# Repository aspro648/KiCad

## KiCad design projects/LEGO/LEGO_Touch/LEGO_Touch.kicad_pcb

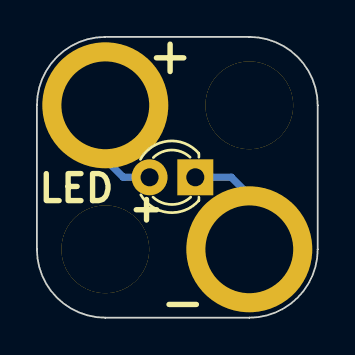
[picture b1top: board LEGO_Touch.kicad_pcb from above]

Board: 2 copper layers, 15.6 x 15.6 mm, 5 parts (0 on the bottom side), 2 nets.

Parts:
D1: LED; LED-3MM
P1, P2, P3, P4: Pad; Lego_Pad

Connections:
unnamed: D1.1, P4.1
unnamed: D1.2, P1.1

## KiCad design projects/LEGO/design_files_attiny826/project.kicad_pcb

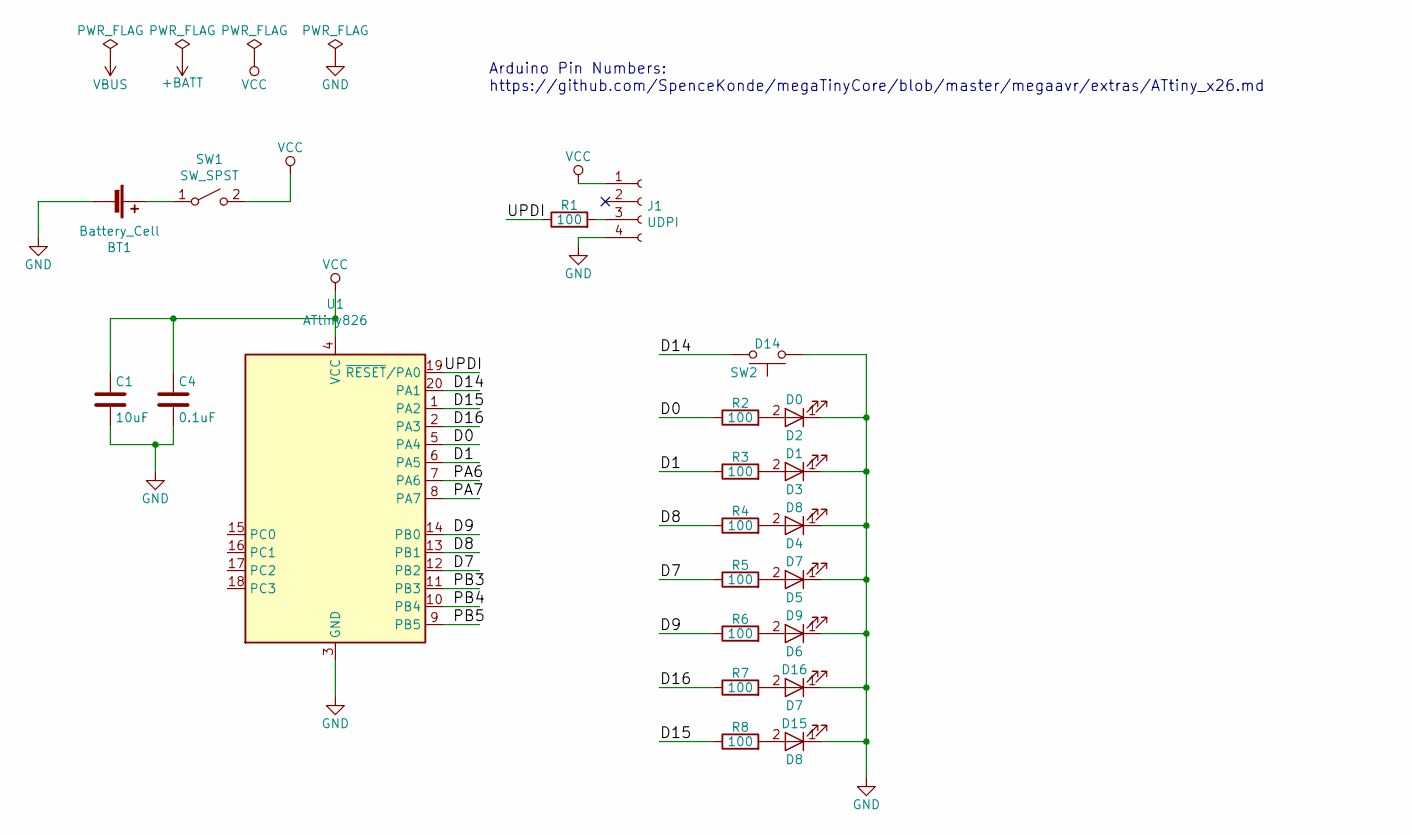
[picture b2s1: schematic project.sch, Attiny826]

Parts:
BT1: Battery_Cell; BatteryHolder_Keystone_3034_1x20mm
C1: 10uF; C_0805
C4: 0.1uF; C_0603
D2: D0; LED_1206_3216Metric
D3: D1; LED_1206_3216Metric
D4: D8; LED_1206_3216Metric
D5: D7; LED_1206_3216Metric
D6: D9; LED_1206_3216Metric
D7: D16; LED_1206_3216Metric
D8: D15; LED_1206_3216Metric
J1: UDPI; UDPI_header
R1, R2, R3, R4, R5, R6, R7, R8: 100; R_0603
SW1: SW_SPST; SPST_SMD
SW2: D14; EVQ-P7A
U1: ATtiny826; VQFN-20-1EP_3x3mm_P0.4mm_EP1.7x1.7mm

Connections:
/D0: R2.1, U1.5 (PA4)
/D1: R3.1, U1.6 (PA5)
/D7: R5.1, U1.12 (PB2)
/D8: R4.1, U1.13 (PB1)
/D9: R6.1, U1.14 (PB0)
/D14: SW2.2, U1.20 (PA1)
/D15: R8.1, U1.1 (PA2)
/D16: R7.1, U1.2 (PA3)
/PA6: U1.7 (PA6)
/PA7: U1.8 (PA7)
/PB3: U1.11 (PB3)
/PB4: U1.10 (PB4)
/PB5: U1.9 (PB5)
/UPDI: R1.1, U1.19 (~RESET~/PA0)
GND: BT1.2 (-), C1.2, C4.2, D2.1 (K), D3.1 (K), D4.1 (K), D5.1 (K), D6.1 (K), D7.1 (K), D8.1 (K), J1.4, SW2.1, U1.3 (GND), U1.21 (GND)
unnamed: BT1.1 (+), SW1.1 (A)
unnamed: D2.2 (A), R2.2
unnamed: D3.2 (A), R3.2
unnamed: D4.2 (A), R4.2
unnamed: D5.2 (A), R5.2
unnamed: D6.2 (A), R6.2
unnamed: D7.2 (A), R7.2
unnamed: D8.2 (A), R8.2
unnamed: J1.3, R1.2
VCC: C1.1, C4.1, J1.1, SW1.2 (B), U1.4 (VCC)

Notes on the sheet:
Arduino Pin Numbers: https://github.com/SpenceKonde/megaTinyCore/blob/master/megaavr/extras/ATtiny_x26.md

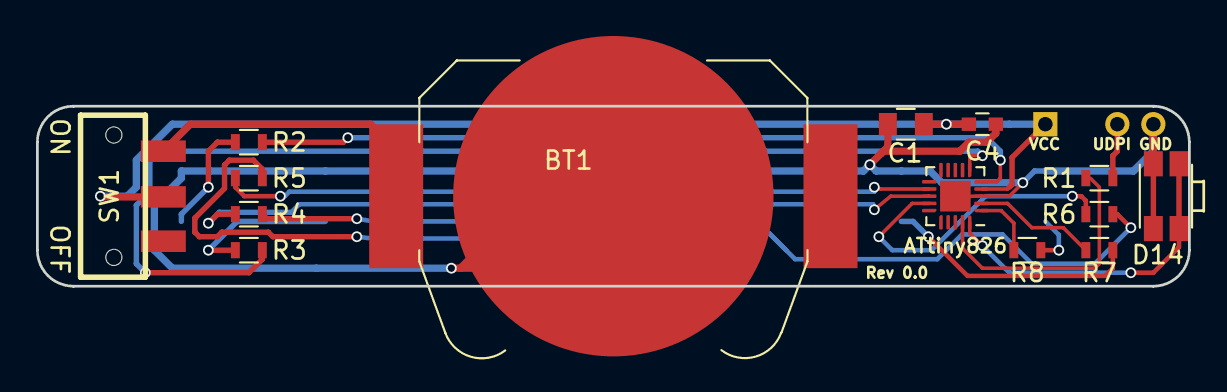
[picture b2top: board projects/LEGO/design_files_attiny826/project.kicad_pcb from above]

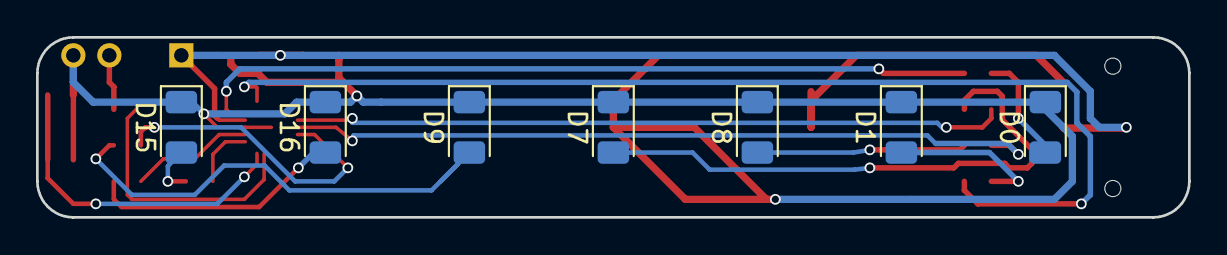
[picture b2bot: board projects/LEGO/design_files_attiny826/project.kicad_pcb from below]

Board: 2 copper layers, 64.0 x 10.0 mm, 22 parts (7 on the bottom side), 20 nets.

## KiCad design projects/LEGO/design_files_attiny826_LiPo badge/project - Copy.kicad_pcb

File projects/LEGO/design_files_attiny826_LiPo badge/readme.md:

Attiny826 Name Tag

Bill Of Materials
----------------

- 1 ea., Perfect Purple PCB from OSH Park from [design_files/project.kicad_pcb](project.kicad_pcb) file.
- 1 ea., Attiny826 IC MCU 8BIT 8KB FLASH 20VQFN, https://www.digikey.com/short/b9cq02np
- 3 ea., CAP CER 10uF 50V 0805,
- 1 ea., CAP CER 0.1uF 0605
- 1 ea., 3.7V LiPo (VERIFY CONNECTOR AND POLARITY).
- 1 ea., CONN RCPT MICRO USB R/A SMD, Molex 1050170001, https://www.digikey.com/short/jb2205
- 1 ea., PTC RESET FUSE 15V 100MA 0805, Bel Fuse 0ZCK0010FF2G, https://www.digikey.com/short/v24142q9
- 1 ea., JST SH CONN HEADER SMD R/A 2POS 1MM, SM02B-SRSS-TB(LF)(SN), https://www.digikey.com/short/z4vw0z
- 1 ea., CONN HOUSING SH 2POS 1MM WHITE, SHR-02V-S-B, https://www.digikey.com/short/0b2m0rpt
- 12 ea., RES SMD 100 OHM 5% 1/8W 0402,
- 2 ea., RES SMD 1K OHM, 0603
- 2 ea., RES SMD 10K OHM, 0603
- 1 ea., SMD SPST switch, C&K JS102011SCQN, https://www.digikey.com/short/5m7mwm1b

- LEDs: 
    - 3 ea., LED RED DIFFUSED 0603 SMD (CHG)
	- 1 ea., LED GREEN DIFFUSE 0603 SMD (DONE)
    - 12 ea., LED WHITE? SMD 0402, https://www.digikey.com/short/d4vn9ddn
	- 1 ea., NeoPixel Nano 2020, https://www.adafruit.com/product/4684 or https://www.digikey.com/short/480tzjf0

Revisions
----------------
- Revision 0.0

License
----------------
[Attribution-ShareAlike 3.0 United States (CC BY-SA 3.0 US)](https://creativecommons.org/licenses/by-sa/3.0/us/)

You are free to:

- Share — copy and redistribute the material in any medium or format
- Adapt — remix, transform, and build upon the material

Under the following terms:

- Attribution — You must give appropriate credit, provide a link to the license, and indicate if changes were made. You may do so in any reasonable manner, but not in any way that suggests the licensor endorses you or your use.
- ShareAlike — If you remix, transform, or build upon the material, you must distribute your contributions under the same license as the original.

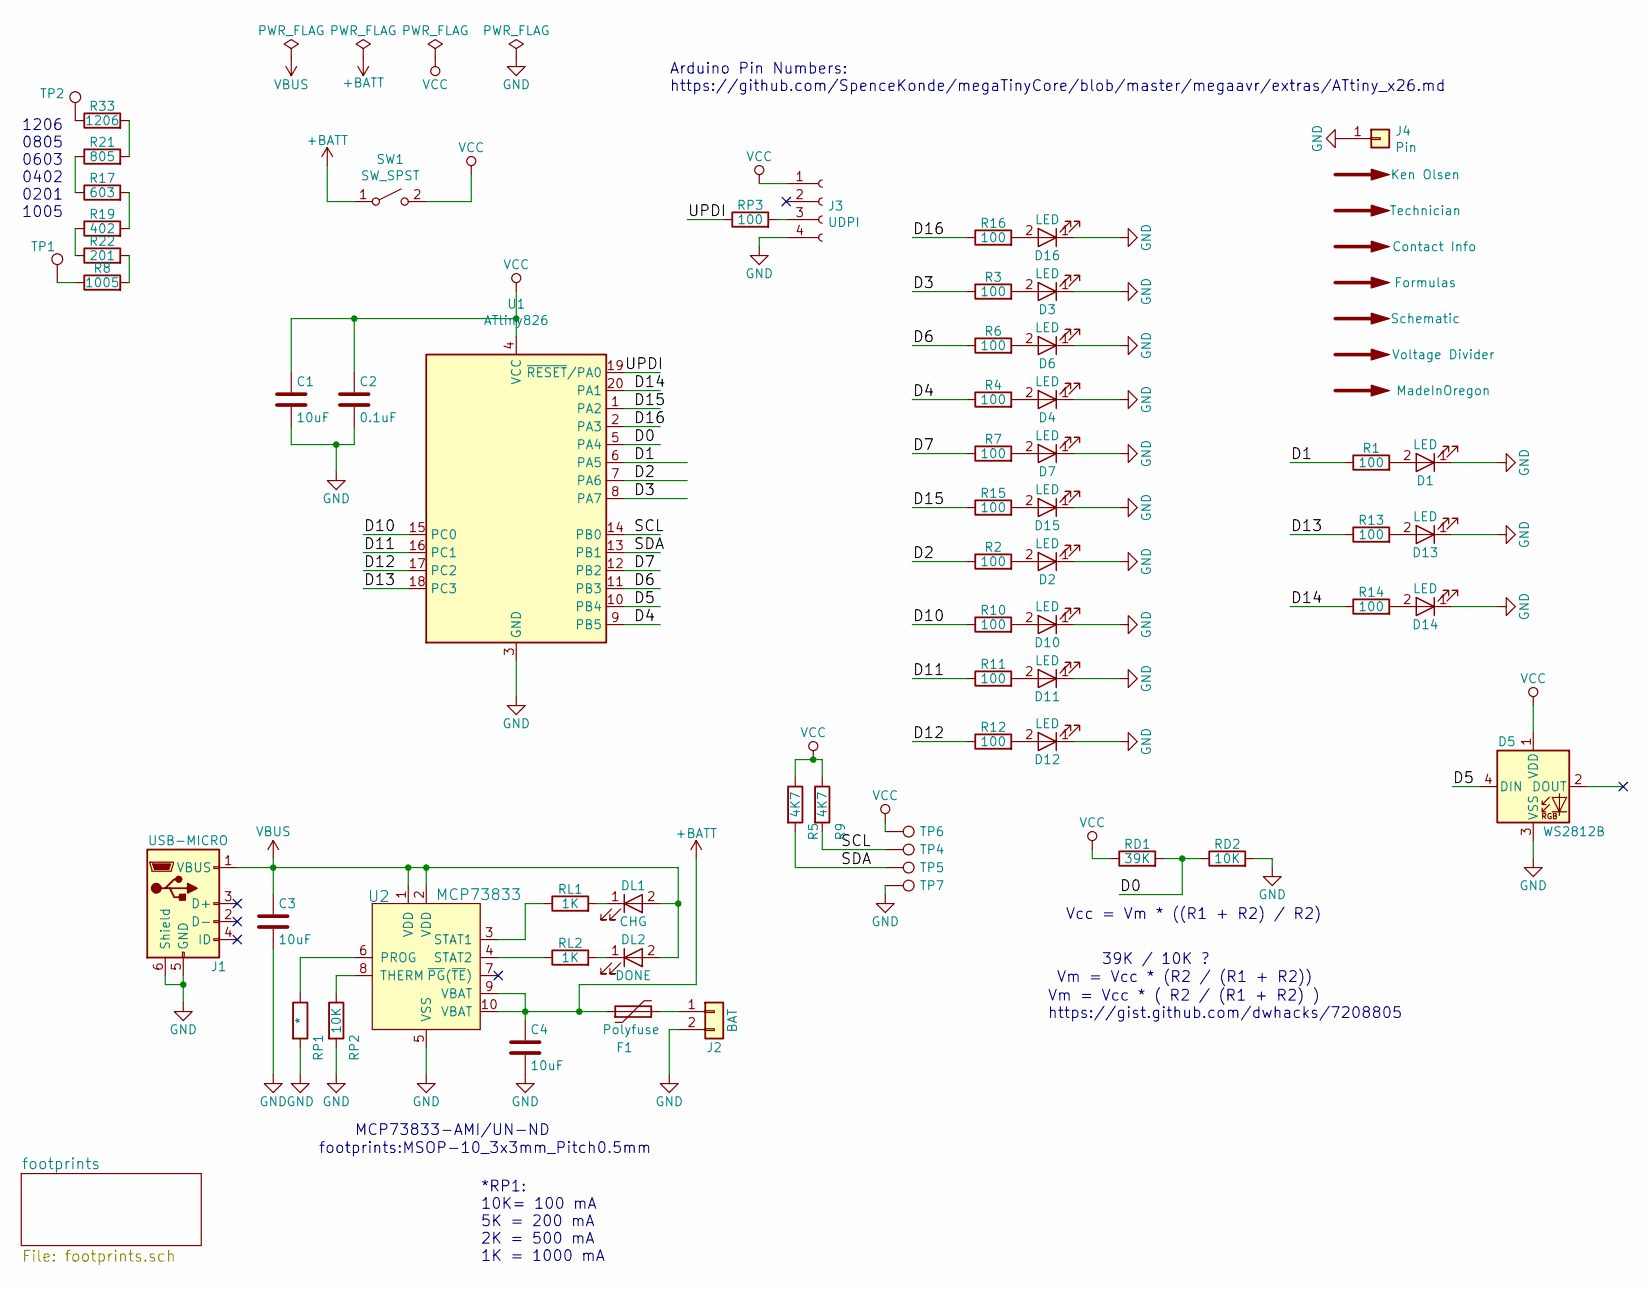
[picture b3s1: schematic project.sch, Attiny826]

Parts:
C1, C3, C4: 10uF; C_0805
C2: 0.1uF; C_0603
D1, D2, D3, D4, D6, D7, D10, D11, D12, D13, D14, D15, D16: LED; LED_0402_1005Metric
D5: WS2812B; WS2812B-2020
DL1: CHG; LED_0603
DL2: DONE; LED_0603
F1: Polyfuse; Fuse_0805_2012Metric
J1: USB-MICRO; USB_Micro-B_Molex-105017-0001
J2: BAT; JST_SH_SM02B-SRSS-TB_02x1.00mm_Angled
J3: UDPI; UDPI_header
J4: Pin; Pin_holder_SMD
R1, R2, R3, R4, R6, R7, R10, R11, R12, R13, R14, R15, R16: 100; R_0402_1005Metric
R5, R9: 4K7; R_0603
R8: 1005; R_01005_0402Metric
R17: 603; R_0603_1608Metric
R19: 402; R_0402
R21: 805; R_0805_2012Metric
R22: 201; R_0201_0603Metric
R33: 1206; R_1206_3216Metric
RD1: 39K; R_0402_1005Metric
RD2: 10K; R_0402_1005Metric
RL1, RL2: 1K; R_0603
RP1: *; R_0603
RP2: 10K; R_0603
RP3: 100; R_0402_1005Metric
SW1: SW_SPST; SPST_SMD
SYM1: Ken Olsen; KenOlsen
SYM2: Technician; ElectronicTechnician
SYM3: Contact Info; contact
SYM4: Formulas; PieChart
SYM5: Schematic; schematic
SYM6: Voltage Divider; schematic2
SYM7: MadeInOregon; MadeInOregonRev25
TP1, TP2: TestPoint; TestPoint_Pad_D1.0mm
TP4: SCL; TestPoint_Pad_D1.0mm
TP5: SDA; TestPoint_Pad_D1.0mm
TP6: VCC; TestPoint_Pad_D1.0mm
TP7: GND; TestPoint_Pad_D1.0mm
U1: ATtiny826; VQFN-20-1EP_3x3mm_P0.4mm_EP1.7x1.7mm
U2: MCP73833; MSOP-10_3x3mm_Pitch0.5mm

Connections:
+BATT: C4.1, F1.1, SW1.1 (A), U2.9 (VBAT), U2.10 (VBAT)
/D0: RD1.2, RD2.1, U1.5 (PA4)
/D1: R1.1, U1.6 (PA5)
/D2: R2.1, U1.7 (PA6)
/D3: R3.1, U1.8 (PA7)
/D4: R4.1, U1.9 (PB5)
/D5: D5.4 (DIN), U1.10 (PB4)
/D6: R6.1, U1.11 (PB3)
/D7: R7.1, U1.12 (PB2)
/D10: R10.1, U1.15 (PC0)
/D11: R11.1, U1.16 (PC1)
/D12: R12.1, U1.17 (PC2)
/D13: R13.1, U1.18 (PC3)
/D14: R14.1, U1.20 (PA1)
/D15: R15.1, U1.1 (PA2)
/D16: R16.1, U1.2 (PA3)
/SCL: R9.2, TP4.1, U1.14 (PB0)
/SDA: R5.2, TP5.1, U1.13 (PB1)
/UPDI: RP3.1, U1.19 (~RESET~/PA0)
GND: C1.2, C2.2, C3.2, C4.2, D1.1 (K), D2.1 (K), D3.1 (K), D4.1 (K), D5.3 (VSS), D6.1 (K), D7.1 (K), D10.1 (K), D11.1 (K), D12.1 (K), D13.1 (K), D14.1 (K), D15.1 (K), D16.1 (K), J1.5 (GND), J1.6 (Shield), J2.2, J3.4, J4.1, RD2.2, RP1.2, RP2.2, TP7.1, U1.3 (GND), U1.21 (GND), U2.5 (VSS)
unnamed: D1.2 (A), R1.2
unnamed: D2.2 (A), R2.2
unnamed: D3.2 (A), R3.2
unnamed: D4.2 (A), R4.2
unnamed: D6.2 (A), R6.2
unnamed: D7.2 (A), R7.2
unnamed: D10.2 (A), R10.2
unnamed: D11.2 (A), R11.2
unnamed: D12.2 (A), R12.2
unnamed: D13.2 (A), R13.2
unnamed: D14.2 (A), R14.2
unnamed: D15.2 (A), R15.2
unnamed: D16.2 (A), R16.2
unnamed: DL1.1 (K), RL1.2
unnamed: DL2.1 (K), RL2.2
unnamed: F1.2, J2.1
unnamed: J3.3, RP3.2
unnamed: R8.1, TP1.1
unnamed: R17.1, R21.1
unnamed: R17.2, R19.2
unnamed: R19.1, R22.1
unnamed: R21.2, R33.2
unnamed: R8.2, R22.2
unnamed: R33.1, TP2.1
unnamed: RL1.1, U2.3 (STAT1)
unnamed: RL2.1, U2.4 (STAT2)
unnamed: RP1.1, U2.6 (PROG)
unnamed: RP2.1, U2.8 (THERM)
VBUS: C3.1, DL1.2 (A), DL2.2 (A), J1.1 (VBUS), U2.1 (VDD), U2.2 (VDD)
VCC: C1.1, C2.1, D5.1 (VDD), J3.1, R5.1, R9.1, RD1.1, SW1.2 (B), TP6.1, U1.4 (VCC)

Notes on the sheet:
Arduino Pin Numbers: https://github.com/SpenceKonde/megaTinyCore/blob/master/megaavr/extras/ATtiny_x26.md
*RP1: 10K= 100 mA 5K = 200 mA 2K = 500 mA 1K = 1000 mA
footprints:MSOP-10_3x3mm_Pitch0.5mm
MCP73833-AMI/UN-ND
39K / 10K ?
Vm = Vcc * ( R2 / (R1 + R2) ) https://gist.github.com/dwhacks/7208805
1206 0805 0603 0402 0201 1005
Vm = Vcc * (R2 / (R1 + R2))
Vcc = Vm * ((R1 + R2) / R2)

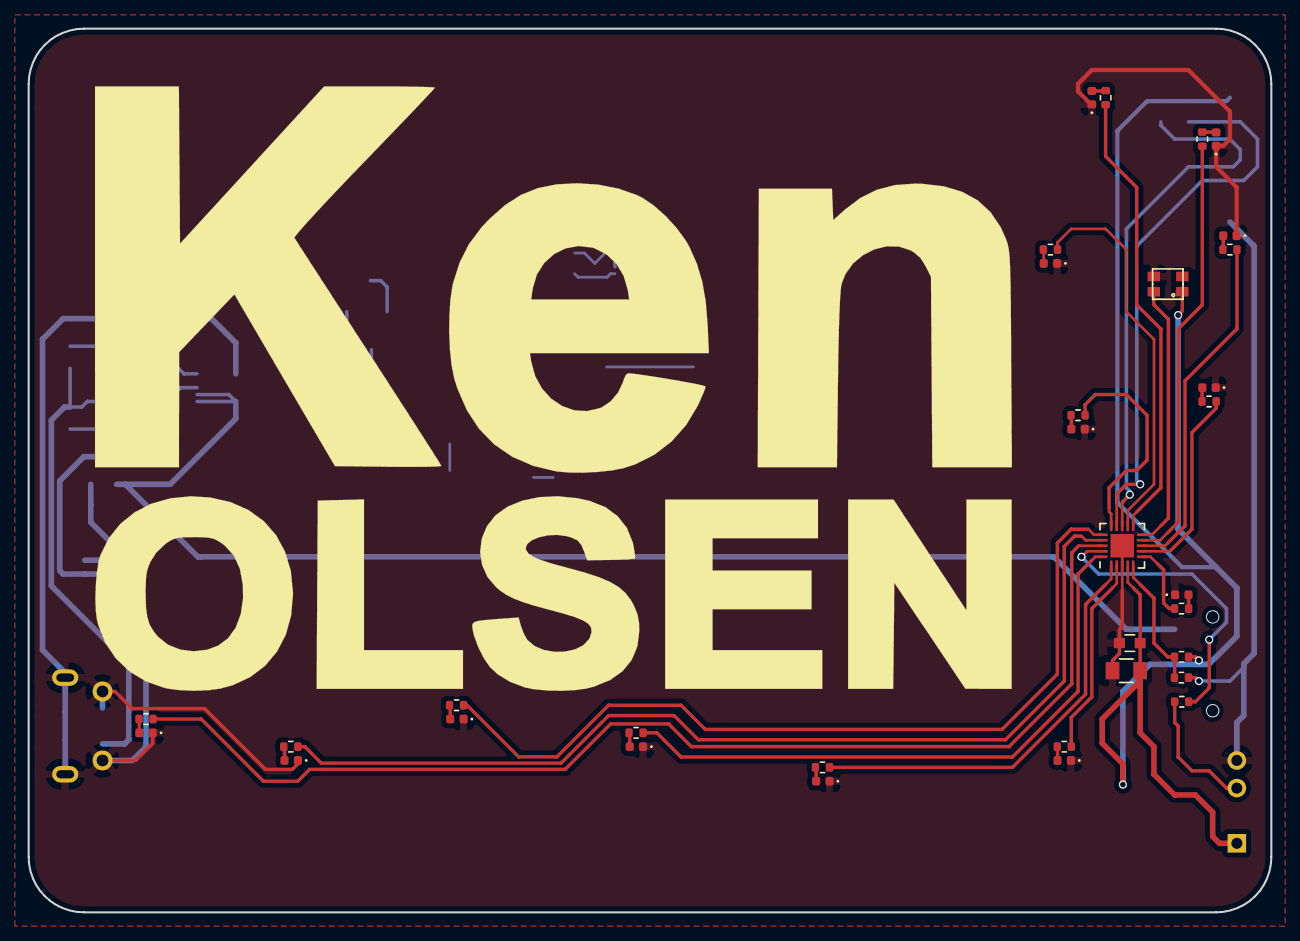
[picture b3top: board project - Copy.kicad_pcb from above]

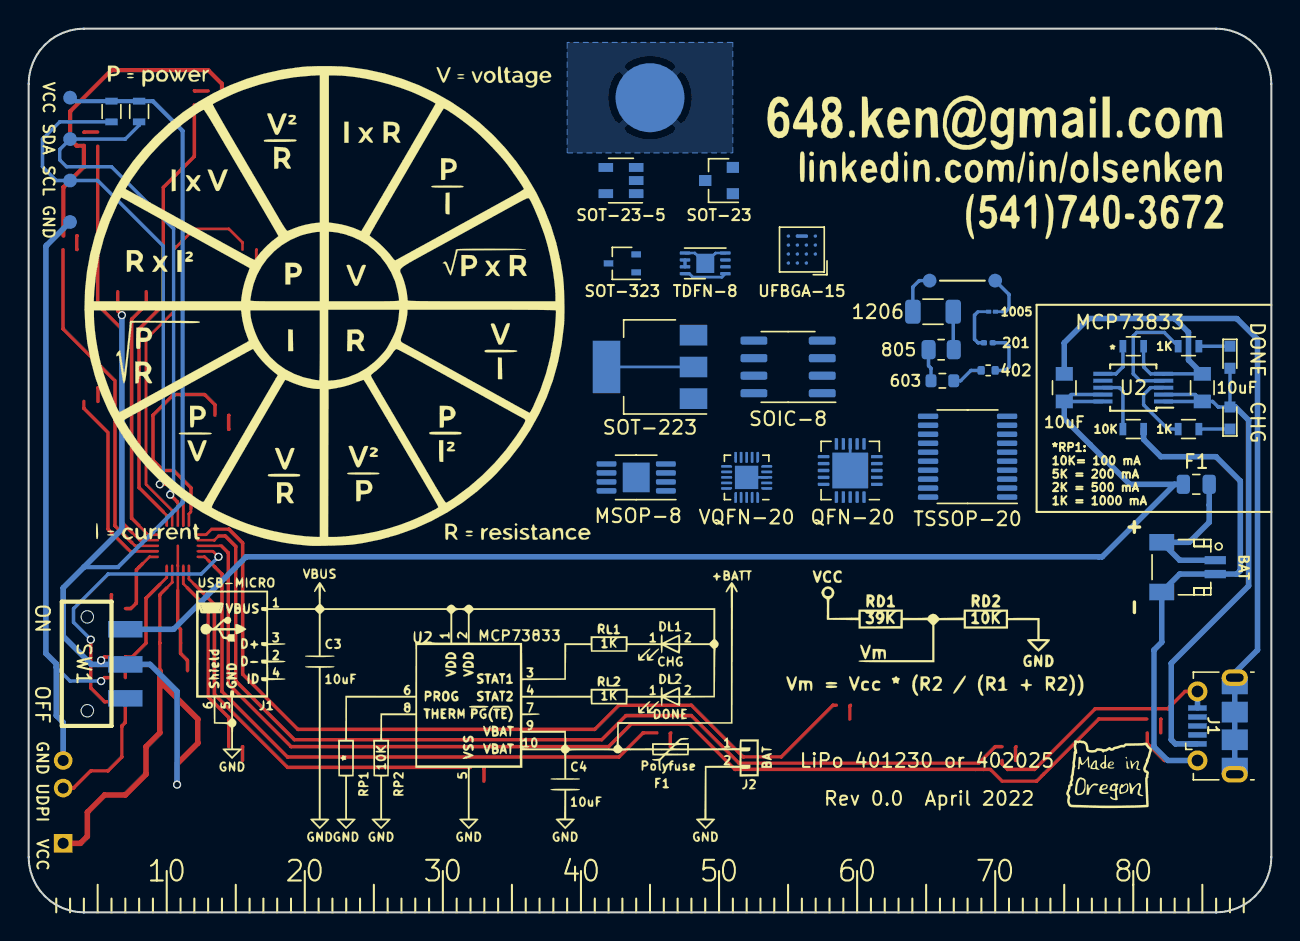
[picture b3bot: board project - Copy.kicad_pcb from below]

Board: 2 copper layers, 90.0 x 64.0 mm, 80 parts (43 on the bottom side), 57 nets.

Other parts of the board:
Q1: SOT-23
Q2: SOT-323; SOT-323_SC-70
Q3: SOT-223
U3: VQFN-20; VQFN-20-1EP_3x3mm_P0.4mm_EP1.7x1.7mm
U4: UFBGA-15; UFBGA-15_3.0x3.0mm_Layout4x4_P0.65mm
U5: QFN-20; QFN-20-1EP_4x4mm_P0.5mm_EP2.6x2.6mm
U6: TSSOP-20; TSSOP-20_4.4x6.5mm_P0.65mm
U7: SOT-23-5
U8: TDFN-8; TDFN-8-1EP_3x2mm_P0.5mm_EP1.3x1.4mm
U9: MSOP-8; MSOP-8-1EP_3x3mm_P0.65mm_EP1.95x2.15mm
U10: SOIC-8; SOIC-8_3.9x4.9mm_P1.27mm

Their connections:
unnamed: Q3.2, Q3.4
unnamed: U3.3, U3.21
unnamed: U4.D2, U4.D3
unnamed: U5.8, U5.21
unnamed: U8.1, U8.8
unnamed: U8.4, U8.5, U8.9
unnamed: U8.6, U8.7

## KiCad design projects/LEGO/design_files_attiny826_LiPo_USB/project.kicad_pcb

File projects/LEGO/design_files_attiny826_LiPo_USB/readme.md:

Beetje Blok 32U4

Based on Adafruit's [ItsyBitsy](https://learn.adafruit.com/introducting-itsy-bitsy-32u4) and SparkFun's [Pro Micro](https://www.sparkfun.com/products/12587) 3.3V/8Mhz versions.

Project page on [Hack-A-Day](https://hackaday.io/project/160638-beetje-bloks).

This is the first "dev blok" for this proof-of-concept project.  It is a KiCad mash-up of Adafruit's [ItsyBity](https://learn.adafruit.com/introducting-itsy-bitsy-32u4) and SparkFun's [Pro Micro](https://www.sparkfun.com/products/12587), jammed into Hack-A-Day's [Once Square Inch Scheme](https://hackaday.io/project/7813-the-square-inch-project) ("HADOSIS").

Bill Of Materials
----------------
  
- 1 ea., Perfect Purple PCB from OSH Park, with not so perfect kicad.pcb file.
- 1 ea., U1, ATMEGA32U4-AU, IC MCU 8BIT 32KB FLASH 44TQFP, https://www.digikey.com/short/jb25pc
- 1 ea., U2, IC REG LINEAR 3.3V 150MA SOT23-5, MIC5225-3.3YM5-TR, https://www.digikey.com/short/jb2rq8
- 3 ea,, C1-C3 10uF SMD 0805, https://www.digikey.com/short/j5d39w 
- 1 ea., C4 1uF SMD 0603, https://www.digikey.com/short/j5d397
- 3 ea., D1-D3 0603 SMD LED, https://www.digikey.com/short/j5h3h5
- 2 ea., D4, D5 DIODE SCHOTTKY 20V 1A SOD123FL, MBR120ESFT1G, https://www.digikey.com/short/jnqvz9
- 1 ea., F1 PTC 1206, Bel 0ZCJ0025AF2E, https://www.digikey.com/short/jfcbc8
- 3 ea., R1-R3 1K Ohm 0603 SMD resistor, https://www.digikey.com/short/jfcb32
- 2 ea., R4, R5 Resistor 4.7K SMD 0603, https://www.digikey.com/short/j2d05w
- 2 ea., R6, R7, 22 Ohm 5% 0603 SMD resistor, https://www.digikey.com/short/jfcbtj
- 1 ea., R8 100K ohm 0603 SMD resistor, https://www.digikey.com/short/jnqvjq
- 2 ea., SW1, Sw2 RA Tactile SPST, Pansonic EVQ-P7J01P, https://www.digikey.com/short/jfwprn
- 1 ea., X1 CONN RCPT MICRO USB R/A SMD, Molex 1050170001, https://www.digikey.com/short/jb2205
- 1 ea., Y1 Resonator 8MHZ, CSTNE8M00G55Z000R0, https://www.digikey.com/short/jb22j1

Headers:
--------

- J2, CONN HEADER FEMALE 6POS .1" GOLD, https://www.digikey.com/short/jfcnz3
- J4, CONN HEADER FEMALE 8POS .1" GOLD, https://www.digikey.com/short/jfcnzj
   or
- Stacking Arduino headers like https://www.digikey.com/short/jfcnz3
   or
- 1 ea., 64-pin header(enough for 4.5 boards) Mill-max 311-43-164-41-001000, https://www.digikey.com/short/jnqdm2
   or
- 1 ea., CONN SOCKET SIP 8POS GOLD, Mill-Max 315-47-108-41-001000, https://www.digikey.com/short/jn51q5
- 1 ea., CONN SOCKET SIP 6POS GOLD, Mill-Max 315-47-106-41-001000, https://www.digikey.com/short/jn5188

Revisions
----------------
- Revision 0.1 - Diodes and polyfuse to front.
- Revision 0.2 - I2C pullups, added SW2, enlarge holes for headers.
- Revision 0.3 - Pinout change, rerouted. NOT BACKWARD COMPATIBLE.
- Revision 0.4 - Renumbering, reordering references.
- Revision 0.5 - Enlarge holes again (for 801 series headers).
                 Switch to global beetje_footprints library.

License
----------------
[Attribution-ShareAlike 3.0 United States (CC BY-SA 3.0 US)](https://creativecommons.org/licenses/by-sa/3.0/us/)

You are free to:

- Share — copy and redistribute the material in any medium or format
- Adapt — remix, transform, and build upon the material

Under the following terms:

- Attribution — You must give appropriate credit, provide a link to the license, and indicate if changes were made. You may do so in any reasonable manner, but not in any way that suggests the licensor endorses you or your use.
- ShareAlike — If you remix, transform, or build upon the material, you must distribute your contributions under the same license as the original.

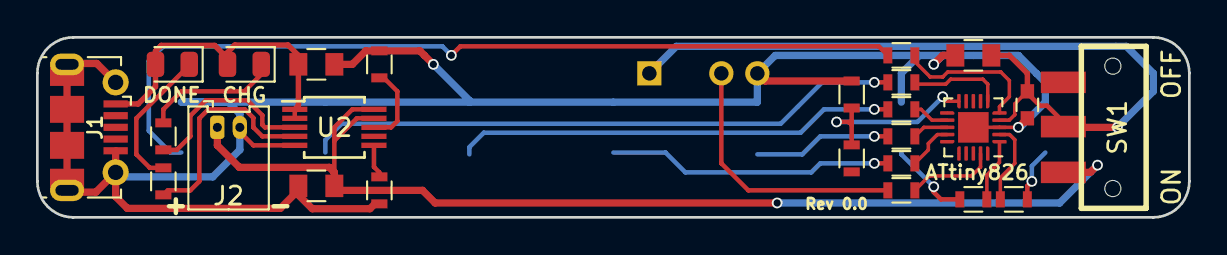
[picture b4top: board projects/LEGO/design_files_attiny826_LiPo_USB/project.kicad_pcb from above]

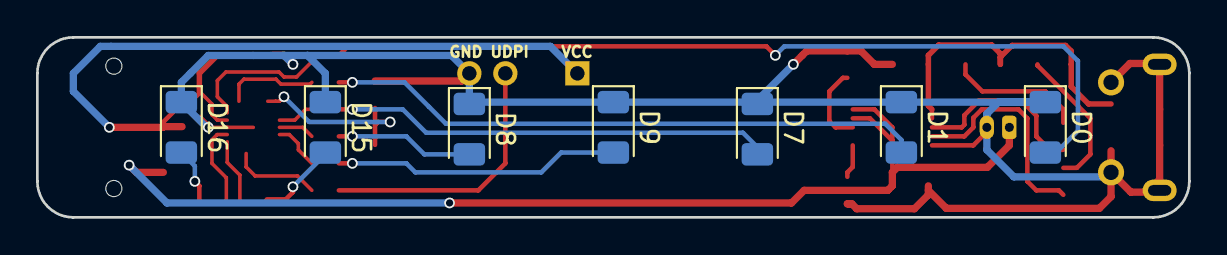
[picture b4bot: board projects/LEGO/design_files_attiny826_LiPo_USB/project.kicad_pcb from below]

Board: 2 copper layers, 64.0 x 10.0 mm, 33 parts (8 on the bottom side), 27 nets.

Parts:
C1, C3, C4: 10uF; C_0805
C2: 0.1uF; C_0603
D1: CHG; LED_0805_2012Metric
D2: DONE; LED_0805_2012Metric
D3: D0; LED_1206_3216Metric
D4: D1; LED_1206_3216Metric
D5: D8; LED_1206_3216Metric
D6: D7; LED_1206_3216Metric
D7: D9; LED_1206_3216Metric
D8: D16; LED_1206_3216Metric
D9: D15; LED_1206_3216Metric
J1: USB-MICRO; USB_Micro-B_Molex-105017-0001
J2: BAT; Molex_PicoBlade_53048-0210_1x02_P1.25mm_Horizontal
J3: UDPI; UDPI_header
R1: 1; R_0603
R2: 2; R_0603
R3, R6, R7, R8, R9, R10, R11, R12: 100; R_0603
R4, R5: 1K; R_0603
R13, R14: 10K; R_0603
SW1: SW_SPST; SPST_SMD
U1: ATtiny826; VQFN-20-1EP_3x3mm_P0.4mm_EP1.7x1.7mm
U2: MCP73833; MSOP-10_3x3mm_Pitch0.5mm

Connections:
+BATT: C4.1, J2.1, SW1.1, U2.9, U2.10
/A5: R1.2, R2.1, U1.10
/D0: R6.1, U1.5
/D1: R7.1, U1.6
/D7: R9.1, U1.12
/D8: R8.1, U1.13
/D9: R10.1, U1.14
/D15: R11.1, U1.1
/D16: R12.1, U1.2
/UPDI: R3.1, U1.19
GND: C1.2, C2.2, C3.2, C4.2, D3.1, D4.1, D5.1, D6.1, D7.1, D8.1, D9.1, J1.5, J1.6, J2.2, J3.4, R2.2, R13.2, R14.2, U1.3, U1.21, U2.5
unnamed: D1.1, R4.2
unnamed: D2.1, R5.2
unnamed: D3.2, R6.2
unnamed: D4.2, R7.2
unnamed: D5.2, R8.2
unnamed: D6.2, R9.2
unnamed: D7.2, R10.2
unnamed: D8.2, R12.2
unnamed: D9.2, R11.2
unnamed: J3.3, R3.2
unnamed: R4.1, U2.3
unnamed: R5.1, U2.4
unnamed: R13.1, U2.6
unnamed: R14.1, U2.8
VBUS: C3.1, D1.2, D2.2, J1.1, U2.1, U2.2
VCC: C1.1, C2.1, J3.1, SW1.2, U1.4

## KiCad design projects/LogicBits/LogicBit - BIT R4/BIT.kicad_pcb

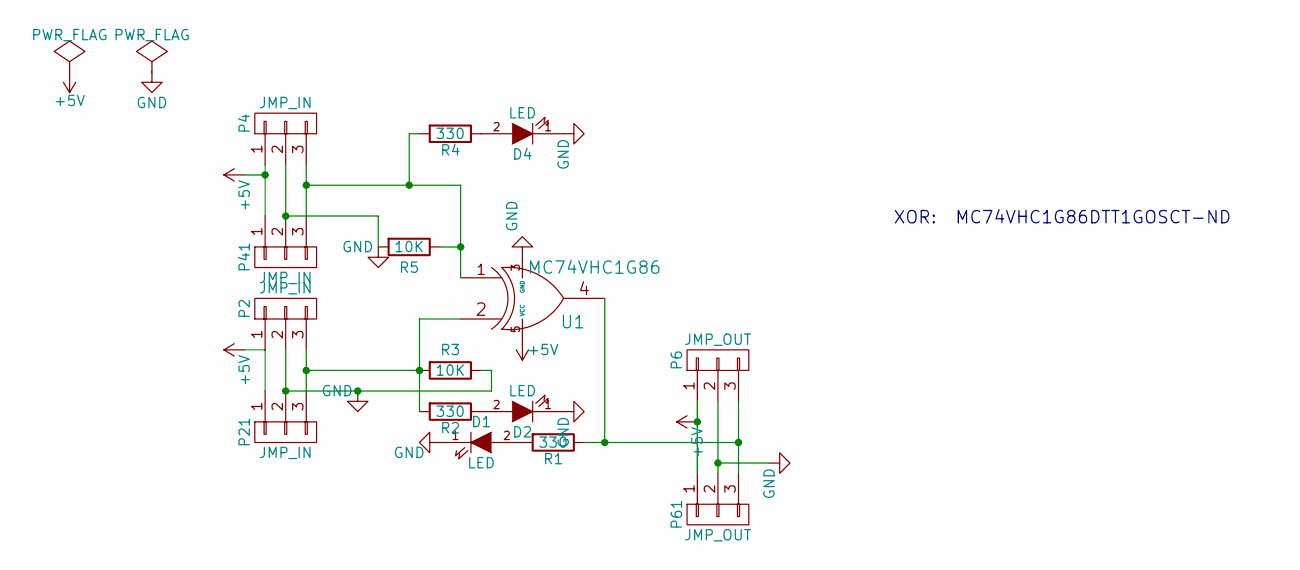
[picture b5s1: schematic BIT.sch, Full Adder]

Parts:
D1, D2, D4: LED; LED-1206
P2, P4: JMP_IN; Socket_Strip_Angled_1x03
P6: JMP_OUT; Pin_Header_Angled_1x03
P21, P41: JMP_IN; Socket_Strip_Straight_1x03
P61: JMP_OUT; Pin_Header_Straight_1x03
R1: 330; pin_socket_3
R2, R4: 330; R_1206
R3, R5: 10K; R_1206
U1: MC74VHC1G86; SOT-23-5

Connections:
+5V: P2.1, P4.1, P6.1, P21.1, P41.1, P61.1, U1.5 (VCC)
GND: D1.1 (K), D2.1 (K), D4.1 (K), P2.2, P4.2, P6.2, P21.2, P41.2, P61.2, R3.1, R5.2, U1.3 (GND)
unnamed: D1.2 (A), R1.2
unnamed: D2.2 (A), R2.1
unnamed: D4.2 (A), R4.1
unnamed: P2.3, P21.3, R2.2, R3.2, U1.2
unnamed: P4.3, P41.3, R4.2, R5.1, U1.1
unnamed: P6.3, P61.3, R1.1, U1.4

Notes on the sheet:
XOR: MC74VHC1G86DTT1GOSCT-ND

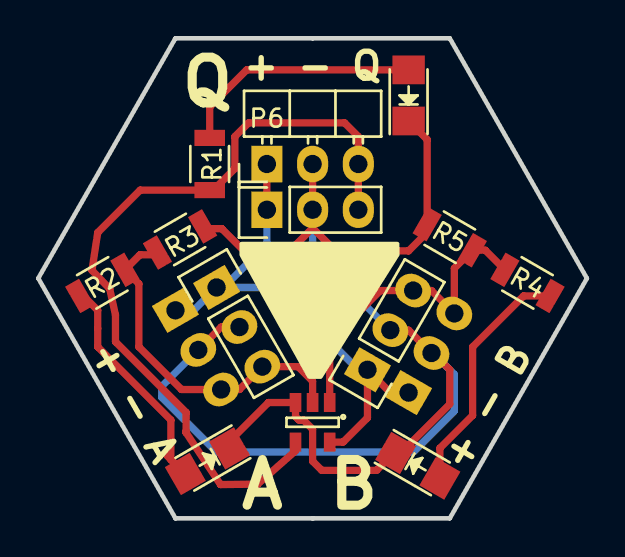
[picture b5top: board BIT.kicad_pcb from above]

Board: 2 copper layers, 30.5 x 26.7 mm, 17 parts (0 on the bottom side), 8 nets.

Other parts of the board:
VAL: MadeInOregonRev25
VAL#2: MB225rev

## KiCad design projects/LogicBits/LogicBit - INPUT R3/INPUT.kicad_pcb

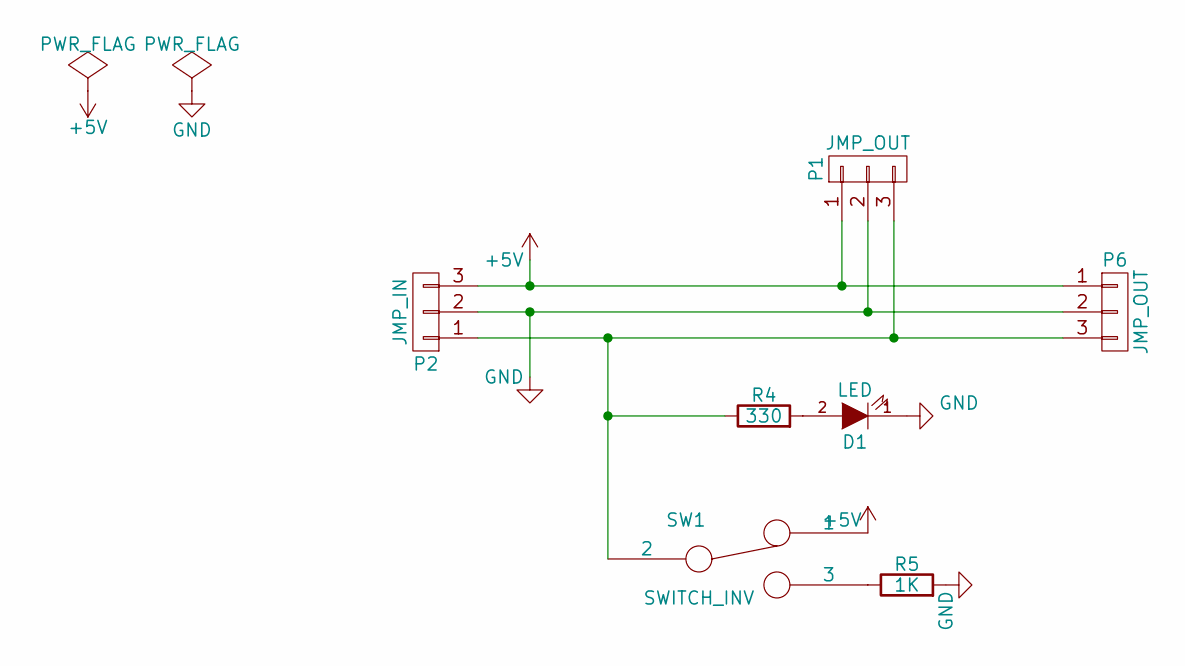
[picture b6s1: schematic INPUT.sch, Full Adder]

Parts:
D1: LED; LED-1206
P1: JMP_OUT; Pin_Header_Straight_1x03
P2: JMP_IN; Pin_Header_Angled_1x03
P6: JMP_OUT; Pin_Header_Angled_1x03
R4: 330; R_1206
R5: 1K; R_1206
SW1: SWITCH_INV; Pin_Header_Straight_1x03

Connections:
+5V: P1.1, P2.3, P6.1, SW1.1
GND: D1.1 (K), P1.2, P2.2, P6.2, R5.2
unnamed: D1.2 (A), R4.2
unnamed: P1.3, P2.1, P6.3, R4.1, SW1.2
unnamed: R5.1, SW1.3

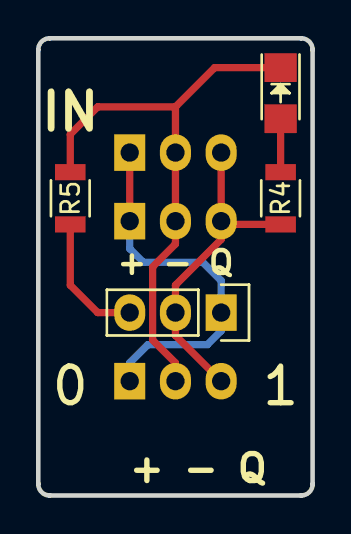
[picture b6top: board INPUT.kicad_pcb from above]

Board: 2 copper layers, 15.2 x 25.4 mm, 9 parts (0 on the bottom side), 5 nets.

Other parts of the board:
Rec: myRec
VAL: MadeInOregonRev25
